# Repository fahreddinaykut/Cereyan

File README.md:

# Cereyan

Battery-powered ESP32-C3 smart ventilation fan with magnetic mounting, ESP-NOW synchronization, USB-C charging, and programmable mobile control.

## Repository Structure

```text
Cereyan/
├─ README.md
├─ LICENSE
├─ hardware/
│  ├─ kicad/
│  ├─ exports/
│  │  ├─ schematic.pdf
│  │  ├─ pcb-top.png
│  │  ├─ pcb-bottom.png
│  │  └─ 3d-render.png
│  ├─ gerbers/
│  └─ bom/
├─ firmware/
│  └─ README.md
├─ mobile-app/
│  └─ README.md
├─ docs/
│  ├─ power-architecture.md
│  ├─ bring-up-checklist.md
│  └─ roadmap.md
└─ images/
```

## GitHub Topics

- esp32-c3
- esp-now
- kicad
- battery-powered
- iot
- camping
- fan-controller
- usb-c
- pcb-design
- embedded-systems

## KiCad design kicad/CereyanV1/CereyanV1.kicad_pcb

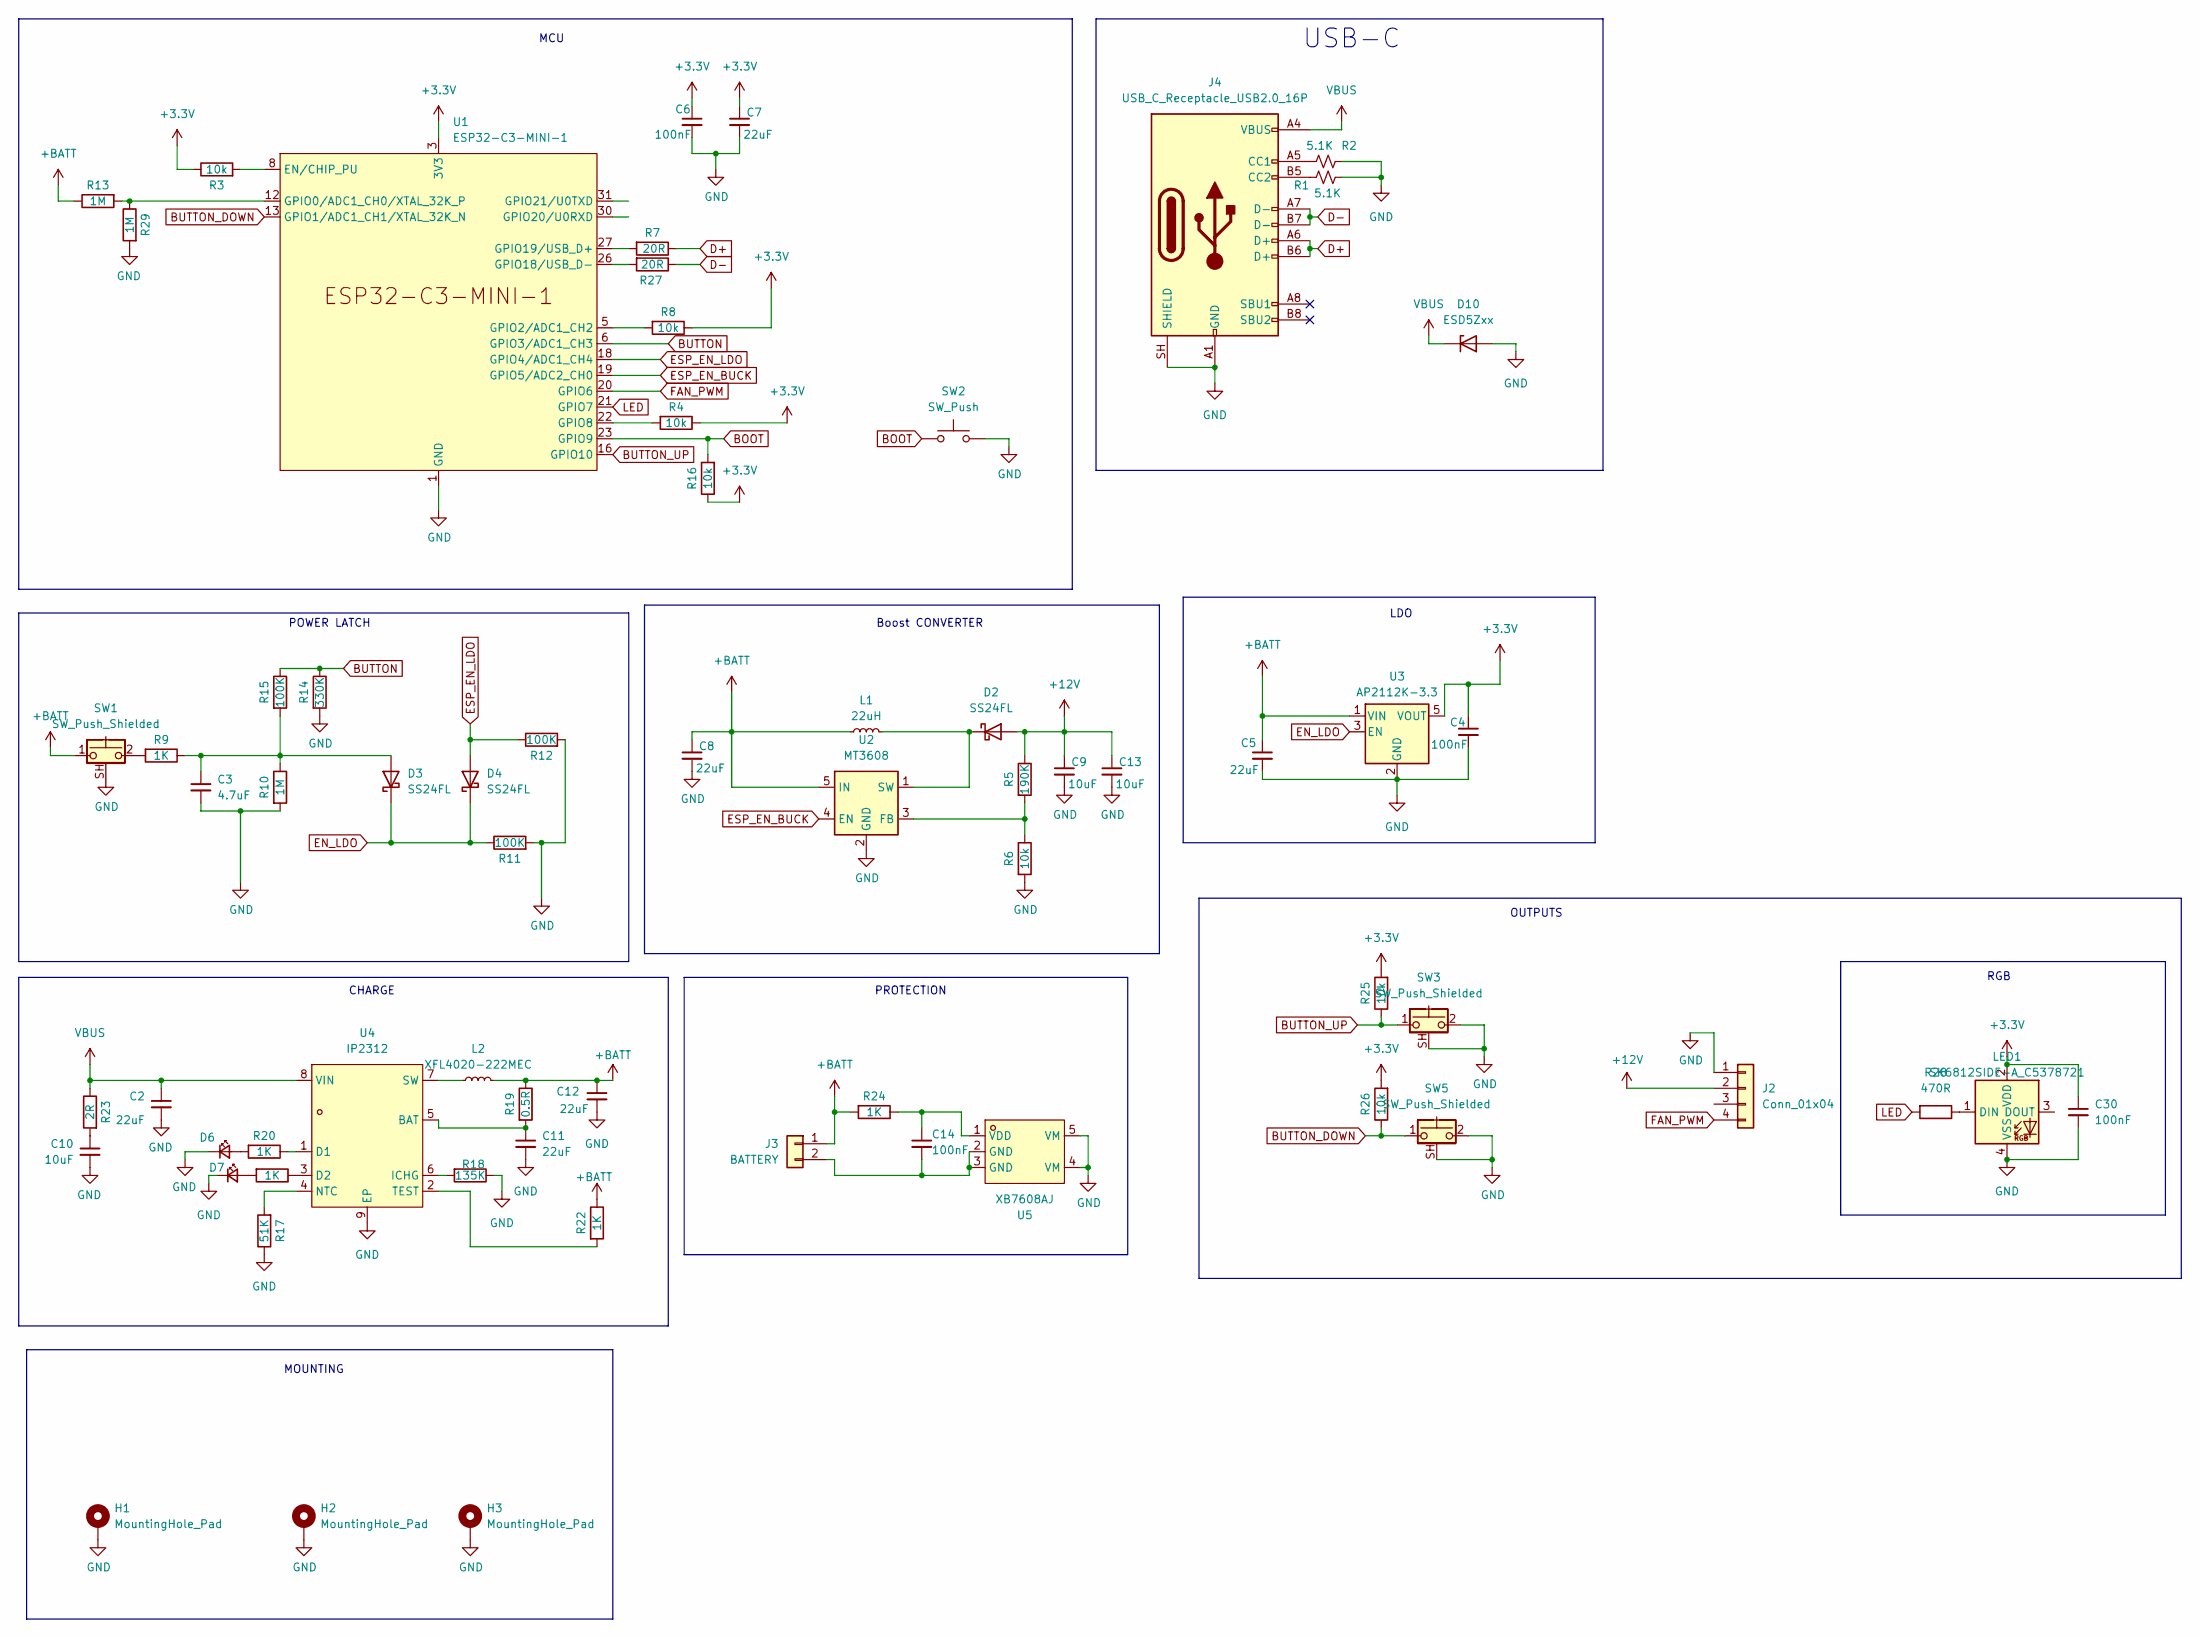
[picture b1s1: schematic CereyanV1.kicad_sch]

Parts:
C2, C5, C7, C8, C11, C12: 22uF; C_0805_2012Metric
C3: 4.7uF; C_0603_1608Metric
C4, C6, C14: 100nF; C_0603_1608Metric
C9, C10, C13: 10uF; C_0805_2012Metric
C30: 100nF; C_0603_1608Metric; LCSC Part Number C1591
D2, D3, D4: SS24FL; D_SOD-123F
D6, D7: LED_Small; LED_0603_1608Metric
D10: ESD5Zxx; D_SOD-523
H1, H3: MountingHole_Pad; MountingHole_2.2mm_M2_DIN965_Pad
H2: MountingHole_Pad; MountingHole_2.2mm_M2
J2: Conn_01x04; JST_EH_B4B-EH-A_1x04_P2.50mm_Vertical
J3: BATTERY; BatteryHolder_Keystone_1042_1x18650
J4: USB_C_Receptacle_USB2.0_16P; USB_C_Receptacle_HRO_TYPE-C-31-M-12
L1: 22uH; L_TechFuse_SL0650
L2: XFL4020-222MEC; L_APV_APH0420
LED1: SK6812SIDE-A_C5378721; LED-SMD_4P-L4.0-W1.6-L; MPN SK6812SIDE-A; LCSC Part C5378721
R1, R2: 5.1K; R_0603_1608Metric
R3, R4, R6, R8, R16, R25, R26: 10k; R_0603_1608Metric
R5: 190K; R_0603_1608Metric
R7, R27: 20R; R_0603_1608Metric
R9, R20, R21, R22, R24: 1K; R_0603_1608Metric
R10, R13, R29: 1M; R_0603_1608Metric
R11, R12, R15: 100K; R_0603_1608Metric
R14: 330K; R_0603_1608Metric
R17: 51K; R_0603_1608Metric
R18: 135K; R_0603_1608Metric
R19: 0.5R; R_0603_1608Metric
R23: 2R; R_0805_2012Metric
R28: 470R; R_0603_1608Metric; LCSC Part Number C2907044
SW1, SW3, SW5: SW_Push_Shielded; SW-TH_K2-1102AQ-C4CW-01
SW2: SW_Push; SW_Push_SPST_NO_Alps_SKRK
U1: ESP32-C3-MINI-1; WIFIM-SMD_ESP32-C3-MINI-1
U2: MT3608; SOT-23-6
U3: AP2112K-3.3; SOT-23-5
U4: IP2312; SOP-8_L4.9-W3.9-P1.27-LS6.0-BL-EP; MPN IP2312U_VSET; LCSC Part C605432
U5: XB7608AJ; CPC-5_L2.6-W2.6-P0.53-LS4.0-BL; MPN XB7608AJ; LCSC Part C2681921

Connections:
+3.3V: C4.1, C6.1, C7.1, C30.1, LED1.2 (VDD), R3.1, R4.1, R8.1, R16.1, R25.2, R26.2, U1.3 (3V3), U3.5 (VOUT)
+12V: C9.1, C13.1, D2.2 (A), J2.2, R5.1
+BATT: C5.1, C8.1, C12.1, J3.1, L1.1, L2.2, R13.1, R19.1, R22.1, R24.2, SW1.1, U2.5 (IN), U3.1 (VIN)
BOOT: R16.2, SW2.1, U1.23 (GPIO9)
BUTTON: R14.1, R15.1, U1.6 (GPIO3/ADC1_CH3)
BUTTON_DOWN: R26.1, SW5.1, U1.13 (GPIO1/ADC1_CH1/XTAL_32K_N)
BUTTON_UP: R25.1, SW3.1, U1.16 (GPIO10)
D+: J4.A6 (D+), J4.B6 (D+), R7.1
D-: J4.A7 (D-), J4.B7 (D-), R27.1
EN_LDO: D3.1 (K), D4.1 (K), R11.1, U3.3 (EN)
ESP_EN_BUCK: U1.19 (GPIO5/ADC2_CH0), U2.4 (EN)
ESP_EN_LDO: D4.2 (A), R12.1, U1.18 (GPIO4/ADC1_CH4)
FAN_PWM: J2.4, U1.20 (GPIO6)
GND: C2.2, C3.2, C4.2, C5.2, C6.2, C7.2, C8.2, C9.2, C10.2, C11.2, C12.2, C13.2, C30.2, D6.1 (K), D7.1 (K), D10.2 (A), H1.1 (1_1), H2.1, H3.1 (1_1), J2.1, J4.A1 (GND), J4.A12 (GND), J4.B1 (GND), J4.B12 (GND), J4.SH (SHIELD), LED1.4 (VSS), R1.2, R2.2, R6.2, R10.2, R11.2, R12.2, R14.2, R17.1, R18.1, R29.2, SW1.SH (B), SW2.2, SW3.2, SW3.SH (B), SW5.2, SW5.SH (B), U1.1 (GND), U1.2 (GND), U1.11 (GND), U1.14 (GND), U1.36 (GND), U1.37 (GND), U1.38 (GND), U1.39 (GND), U1.40 (GND), U1.41 (GND), U1.42 (GND), U1.43 (GND), U1.44 (GND), U1.45 (GND), U1.46 (GND), U1.47 (GND), U1.48 (GND), U1.49 (GND), U1.50 (GND), U1.51 (GND), U1.52 (GND), U1.53 (GND), U2.2 (GND), U3.2 (GND), U4.9 (EP), U5.4 (VM), U5.5 (VM)
LED: R28.2, U1.21 (GPIO7)
unnamed: C10.1, R23.2
unnamed: D2.1 (K), L1.2, U2.1 (SW)
unnamed: C3.1, D3.2 (A), R9.1, R10.1, R15.2
unnamed: D6.2 (A), R20.2
unnamed: D7.2 (A), R21.2
unnamed: C14.2, J3.2, U5.2 (GND), U5.3 (GND)
unnamed: J4.A5 (CC1), R2.1
unnamed: J4.B5 (CC2), R1.1
unnamed: LED1.1 (DIN), R28.1
unnamed: R9.2, SW1.2
unnamed: R3.2, U1.8 (EN/CHIP_PU)
unnamed: R13.2, R29.1, U1.12 (GPIO0/ADC1_CH0/XTAL_32K_P)
unnamed: R8.2, U1.5 (GPIO2/ADC1_CH2)
unnamed: R4.2, U1.22 (GPIO8)
unnamed: R27.2, U1.26 (GPIO18/USB_D-)
unnamed: R7.2, U1.27 (GPIO19/USB_D+)
unnamed: R5.2, R6.1, U2.3 (FB)
unnamed: C11.1, R19.2, U4.5 (BAT)
unnamed: R20.1, U4.1 (D1)
unnamed: R21.1, U4.3 (D2)
unnamed: R18.2, U4.6 (ICHG)
unnamed: R17.2, U4.4 (NTC)
unnamed: L2.1, U4.7 (SW)
unnamed: R22.2, U4.2 (TEST)
unnamed: C14.1, R24.1, U5.1 (VDD)
VBUS: C2.1, D10.1 (K), J4.A4 (VBUS), J4.A9 (VBUS), J4.B4 (VBUS), J4.B9 (VBUS), R23.1, U4.8 (VIN)

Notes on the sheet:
PROTECTION
POWER LATCH
MCU
USB-C
CHARGE
OUTPUTS
Boost CONVERTER
RGB
LDO
MOUNTING

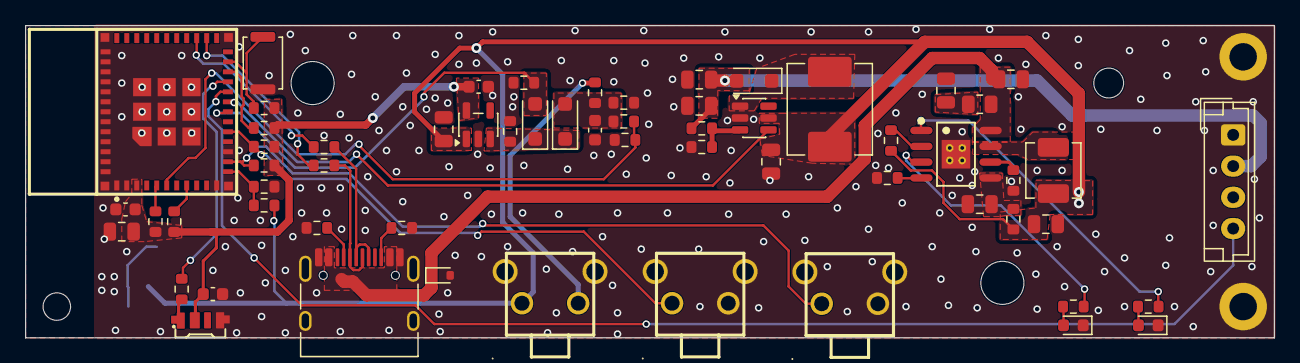
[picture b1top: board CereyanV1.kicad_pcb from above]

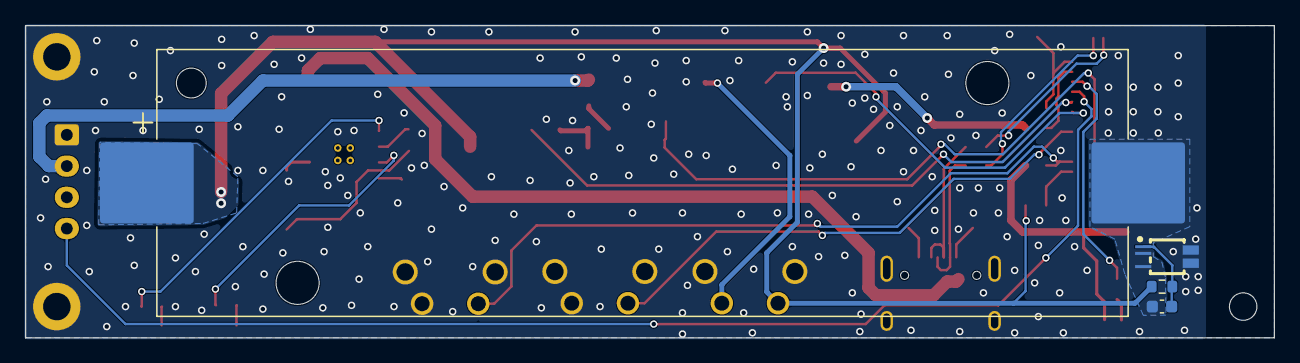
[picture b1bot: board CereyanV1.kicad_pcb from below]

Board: 2 copper layers, 100.0 x 25.0 mm, 67 parts (4 on the bottom side), 41 nets.

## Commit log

2026-06-03 Initial plan
2026-06-03 Update README with detailed project information
    Expanded project details, motivation, features, hardware overview, system concept, current status, repository structure, roadmap, design goals, and license information.
2026-06-03 chore: scaffold Cereyan repository structure
